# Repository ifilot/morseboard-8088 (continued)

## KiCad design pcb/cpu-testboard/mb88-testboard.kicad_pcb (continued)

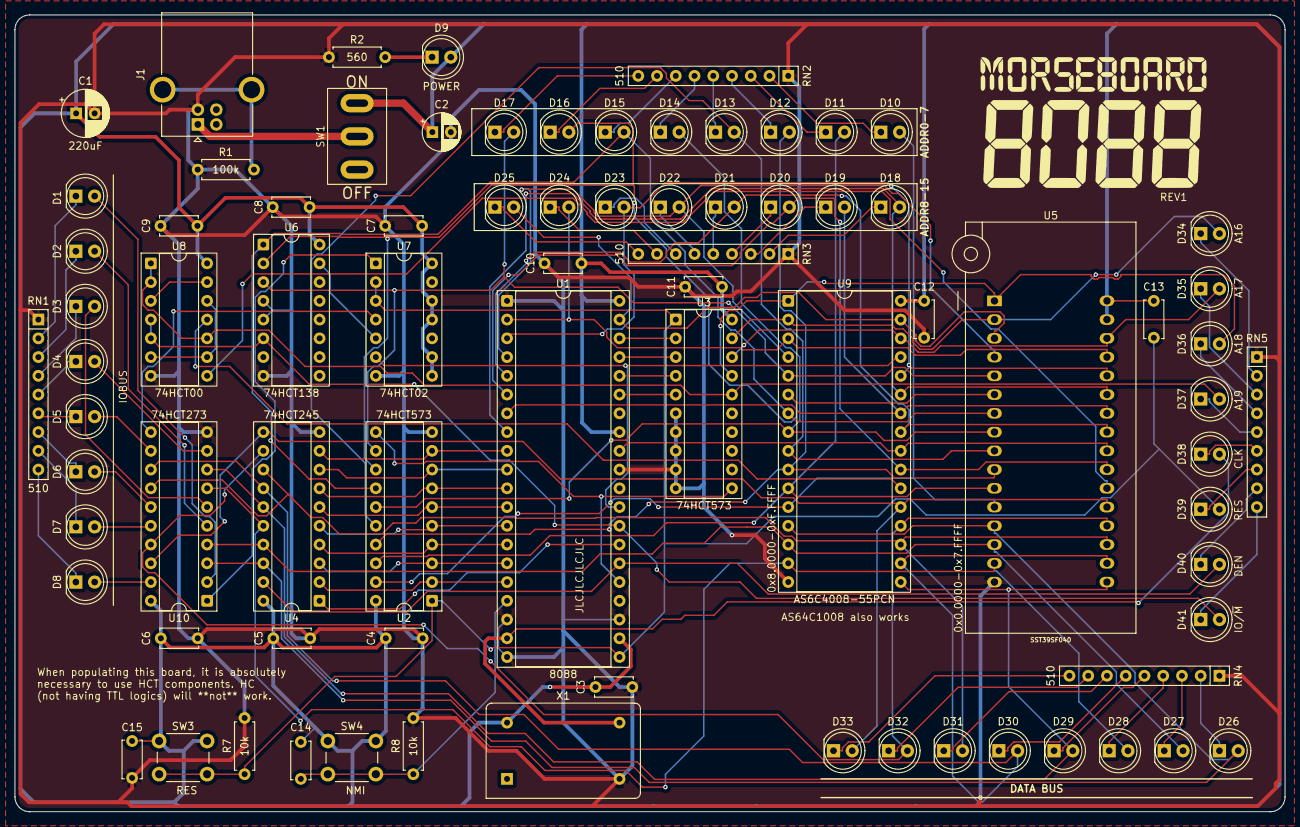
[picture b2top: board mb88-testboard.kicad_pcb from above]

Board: 2 copper layers, 172.1 x 108.0 mm, 80 parts (0 on the bottom side), 109 nets.

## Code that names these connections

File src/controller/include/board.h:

#ifndef MORSEBOARD_CONTROLLER_BOARD_H
#define MORSEBOARD_CONTROLLER_BOARD_H

#include <avr/io.h>
#include <stdbool.h>
#include <stdint.h>

/*
 * Pin map from the controller schematic.
 *
 * RES is active high from the controller's point of view: the board is held in
 * reset by the external pull-down until firmware drives PB0 high.
 */

#define MB_PIN_CD0_PORT PORTC
#define MB_PIN_CD0_DDR DDRC
#define MB_PIN_CD0_PIN PC0

#define MB_PIN_CD1_PORT PORTC
#define MB_PIN_CD1_DDR DDRC
#define MB_PIN_CD1_PIN PC1

#define MB_PIN_CD2_PORT PORTC
#define MB_PIN_CD2_DDR DDRC
#define MB_PIN_CD2_PIN PC2

#define MB_PIN_CD3_PORT PORTC
#define MB_PIN_CD3_DDR DDRC
#define MB_PIN_CD3_PIN PC3

#define MB_PIN_CD4_PORT PORTD
#define MB_PIN_CD4_DDR DDRD
#define MB_PIN_CD4_PIN PD4

#define MB_PIN_CD5_PORT PORTD
#define MB_PIN_CD5_DDR DDRD
#define MB_PIN_CD5_PIN PD5

#define MB_PIN_CD6_PORT PORTD
#define MB_PIN_CD6_DDR DDRD
#define MB_PIN_CD6_PIN PD6

#define MB_PIN_CD7_PORT PORTD
#define MB_PIN_CD7_DDR DDRD
#define MB_PIN_CD7_PIN PD7

#define MB_PIN_BOARD_RESET_PORT PORTB
#define MB_PIN_BOARD_RESET_DDR DDRB
#define MB_PIN_BOARD_RESET_PIN PB0

#define MB_PIN_INTR_PORT PORTB
#define MB_PIN_INTR_DDR DDRB
#define MB_PIN_INTR_PIN PB1

#define MB_PIN_INTA_PORT PORTB
#define MB_PIN_INTA_DDR DDRB
#define MB_PIN_INTA_INPUT PINB
#define MB_PIN_INTA_PIN PB2

#define MB_PIN_VERA_INT_PORT PORTB
#define MB_PIN_VERA_INT_DDR DDRB
#define MB_PIN_VERA_INT_INPUT PINB
#define MB_PIN_VERA_INT_PIN PB3

#define MB_PIN_IO03_PORT PORTB
#define MB_PIN_IO03_DDR DDRB
#define MB_PIN_IO03_INPUT PINB
#define MB_PIN_IO03_PIN PB4

#define MB_PIN_KB_DATA_PORT PORTB
#define MB_PIN_KB_DATA_DDR DDRB
#define MB_PIN_KB_DATA_INPUT PINB
#define MB_PIN_KB_DATA_PIN PB5

#define MB_PIN_ON_BUTTON_PORT PORTC
#define MB_PIN_ON_BUTTON_DDR DDRC
#define MB_PIN_ON_BUTTON_INPUT PINC
#define MB_PIN_ON_BUTTON_PIN PC4

#define MB_PIN_RESET_BUTTON_PORT PORTC
#define MB_PIN_RESET_BUTTON_DDR DDRC
#define MB_PIN_RESET_BUTTON_INPUT PINC
#define MB_PIN_RESET_BUTTON_PIN PC5

#define MB_PIN_CTRL_RXD_PORT PORTD
#define MB_PIN_CTRL_RXD_DDR DDRD
#define MB_PIN_CTRL_RXD_INPUT PIND
#define MB_PIN_CTRL_RXD_PIN PD0

#define MB_PIN_CTRL_TXD_PORT PORTD
#define MB_PIN_CTRL_TXD_DDR DDRD
#define MB_PIN_CTRL_TXD_PIN PD1

#define MB_PIN_KB_CLK_PORT PORTD
#define MB_PIN_KB_CLK_DDR DDRD
#define MB_PIN_KB_CLK_INPUT PIND
#define MB_PIN_KB_CLK_PIN PD2

#define MB_PIN_SERIAL_INT_PORT PORTD
#define MB_PIN_SERIAL_INT_DDR DDRD
#define MB_PIN_SERIAL_INT_INPUT PIND
#define MB_PIN_SERIAL_INT_PIN PD3

static inline void mb_pin_output(volatile uint8_t *ddr, uint8_t bit)
{
    *ddr |= (uint8_t)_BV(bit);
}

static inline void mb_pin_input(volatile uint8_t *ddr, uint8_t bit)
{
    *ddr &= (uint8_t)~_BV(bit);
}

static inline void mb_pin_high(volatile uint8_t *port, uint8_t bit)
{
    *port |= (uint8_t)_BV(bit);
}

static inline void mb_pin_low(volatile uint8_t *port, uint8_t bit)
{
    *port &= (uint8_t)~_BV(bit);
}

static inline bool mb_pin_read(volatile uint8_t *pin_reg, uint8_t bit)
{
    return ((*pin_reg) & (uint8_t)_BV(bit)) != 0;
}

#endif

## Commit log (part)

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2025-05-17 Adding source and revising PCB
2025-05-21 Revising testboard
2025-05-21 Initial commit TL16C550
2025-05-22 Further revising second 8088 SBC prototype
2025-05-23 Updating schematic and board
2025-05-24 Prerouting commit
2025-05-24 Protoype #1 of SBC
2025-06-04 Tuning UART
2025-06-04 Interim commit
2025-06-05 Fixing bugs in PCB design
2025-06-05 Creating new prototype
2025-06-05 Rewriting test rom and adding GA
2025-06-05 Changing name
2025-06-21 Fixing erroneous board layout
2025-07-02 Rewriting routines
2025-07-02 Adding enclosure
2025-07-02 Further building menu and fixing minor mistakes in PCB
2025-07-03 Fixing bug in MorseBoard ROM
2025-07-04 Expanding README.md
2025-07-04 Updating README and adding license
2025-07-04 Fixing bug and updating README
2025-07-06 Polishing schematics
2025-07-13 Removing 8087 based board
2026-06-25 Initial commit VERA daughterboard
2026-06-25 Further shaping board
2026-06-25 Further drawing traces
2026-06-25 Routing VERA prototype
2026-06-28 Building VERA prototype
